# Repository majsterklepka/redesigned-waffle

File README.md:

# redesigned-waffle
mkII AVRISP programmer clone

Projekt klonu wykonany w KiCad. Pewne elementy schematu ideowego wymagają bibliotek, są one dostępne tu: [majsterklepka/expert-waffle](https://github.com/majsterklepka/expert-waffle "eeschema KiCad Libraries"), należy sklonować repo i zainstalować wymagane biblioteki ręcznie.

Klon wykorzystuje framework [LUFA](https://github.com/abcminiuser/lufa "LUFA")

Schemat ideowy => [diagram](/avrisp-mkII-clone/avrisp-mkII-clone.pdf "diagram")

> **2020.04.02**   Dodałem pliki Gerber z rysunkiem płytki drukowanej

## Jak wgrać firmware?

Oczywiście, najpier należy je zdbudować, potem do wgrania firmware wykorzystuje się narzędzie `dfu-util` dostępne chyba w każdej dystrybucji Linuksa i xxxBSD.

## Jak wgrać firmware?

```
dfu-util --upload firmware.hex

gdzie:
firmware.hex - plik HEX z firmware, LUFA/Projects/AVRISP-MKII/

```

Tyle w skrócie, czasem należy podać dodatkowe dane, takie jak `<vendor>:<product>`. Te dane podaje się z opcją `--device`, więcej informacji:

```
dfu-util --help
```

## Credits

Jako taki projekt jest znany w Sieci, istnieje wiele dostępnych modyfikacji, tu jest jedna z nich.

- [MIT](https://raw.githubusercontent.com/majsterklepka/redesigned-waffle/master/LICENSE "MIT License content")

Ten projekt to moja wersja, moja wizja tego popularnego programatora.

_MSc. Paweł Sobótka (SQ7EQE)_

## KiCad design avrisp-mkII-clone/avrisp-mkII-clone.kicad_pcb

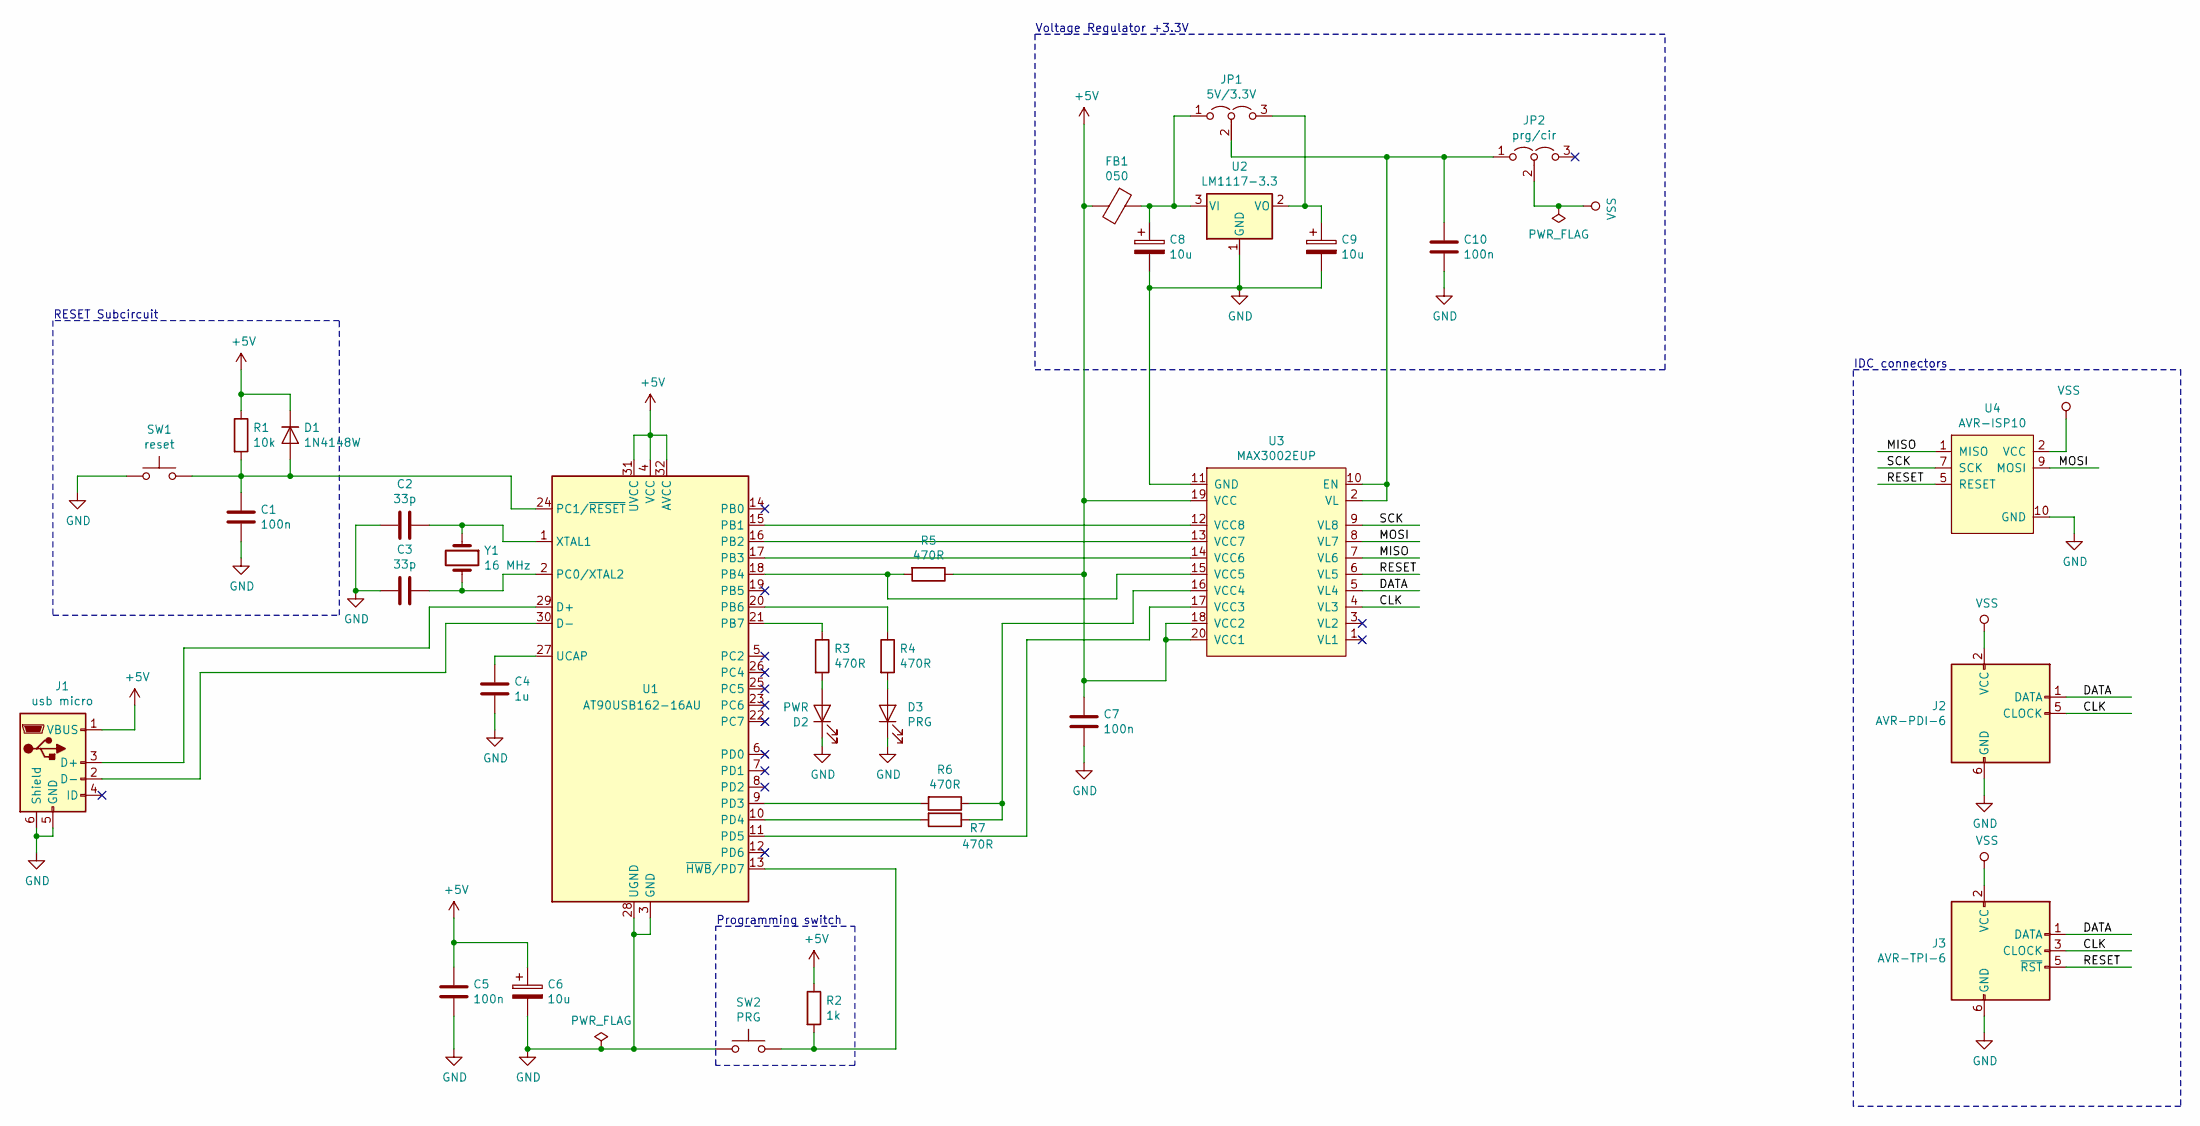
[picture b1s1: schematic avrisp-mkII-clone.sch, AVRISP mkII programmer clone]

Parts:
C1, C5, C7, C10: 100n; C_0805_2012Metric_Pad1.15x1.40mm_HandSolder
C2, C3: 33p; C_0805_2012Metric_Pad1.15x1.40mm_HandSolder
C4: 1u; C_0805_2012Metric_Pad1.15x1.40mm_HandSolder
C6, C8, C9: 10u; CP_EIA-7343-15_Kemet-W_Pad2.25x2.55mm_HandSolder
D1: 1N4148W; D_SOD-123
D2: PWR; LED_D3.0mm
D3: PRG; LED_D3.0mm
FB1: 050; R_1206_3216Metric_Pad1.42x1.75mm_HandSolder
J1: usb micro; USB_Micro-B_Molex_47346-0001
J2: AVR-PDI-6; IDC-Header_2x03_P2.54mm_Vertical
J3: AVR-TPI-6; IDC-Header_2x03_P2.54mm_Vertical
JP1: 5V/3.3V; PinHeader_1x03_P2.54mm_Vertical
JP2: prg/cir; PinHeader_1x03_P2.54mm_Vertical
R1: 10k; R_0805_2012Metric_Pad1.15x1.40mm_HandSolder
R2: 1k; R_0805_2012Metric_Pad1.15x1.40mm_HandSolder
R3, R4, R5, R6, R7: 470R; R_0805_2012Metric_Pad1.15x1.40mm_HandSolder
SW1: reset; SW_PUSH_6mm_H5mm
SW2: PRG; SW_PUSH_6mm_H5mm
U1: AT90USB162-16AU; TQFP-32_7x7mm_P0.8mm
U2: LM1117-3.3; SOT-223
U3: MAX3002EUP; TSSOP-20_4.4x6.5mm_P0.65mm
U4: AVR-ISP10; IDC-Header_2x05_P2.54mm_Vertical
Y1: 16 MHz; Crystal_SMD_HC49-SD_HandSoldering

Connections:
+5V: C5.1, C6.1, C7.2, D1.1 (K), FB1.2, J1.1 (VBUS), R1.1, R2.1, R5.1, U1.4 (VCC), U1.31 (UVCC), U1.32 (AVCC), U3.18 (VCC2), U3.19 (VCC), U3.20 (VCC1)
/CLK: J2.5 (CLOCK), J3.3 (CLOCK), U3.4 (VL3)
/DATA: J2.1 (DATA), J3.1 (DATA), U3.5 (VL4)
/MISO: U3.7 (VL6), U4.1 (MISO)
/MOSI: U3.8 (VL7), U4.9 (MOSI)
/RESET: J3.5 (~RST), U3.6 (VL5), U4.5 (RESET)
/SCK: U3.9 (VL8), U4.7 (SCK)
GND: C1.1, C2.2, C3.2, C4.2, C5.2, C6.2, C7.1, C8.2, C9.2, C10.1, D2.1 (K), D3.1 (K), J1.5 (GND), J1.6 (Shield), J2.6 (GND), J3.6 (GND), SW1.1, SW2.1, U1.3 (GND), U1.28 (UGND), U2.1 (GND), U3.11 (GND), U4.10 (GND)
unnamed: C1.2, D1.2 (A), R1.2, SW1.2, U1.24 (PC1/~RESET)
unnamed: C2.1, U1.1 (XTAL1), Y1.1
unnamed: C3.1, U1.2 (PC0/XTAL2), Y1.2
unnamed: C4.1, U1.27 (UCAP)
unnamed: C8.1, FB1.1, JP1.1 (A), U2.3 (VI)
unnamed: C9.1, JP1.3 (B), U2.2 (VO)
unnamed: C10.2, JP1.2 (C), JP2.1 (A), U3.2 (VL), U3.10 (EN)
unnamed: D2.2 (A), R3.2
unnamed: D3.2 (A), R4.2
unnamed: J1.2 (D-), U1.30 (D-)
unnamed: J1.3 (D+), U1.29 (D+)
unnamed: R2.2, SW2.2, U1.13 (~HWB~/PD7)
unnamed: R3.1, U1.21 (PB7)
unnamed: R4.1, U1.20 (PB6)
unnamed: R5.2, U1.18 (PB4), U3.15 (VCC5)
unnamed: R6.1, R7.1, U3.16 (VCC4)
unnamed: R6.2, U1.9 (PD3)
unnamed: R7.2, U1.10 (PD4)
unnamed: U1.11 (PD5), U3.17 (VCC3)
unnamed: U1.15 (PB1), U3.12 (VCC8)
unnamed: U1.16 (PB2), U3.13 (VCC7)
unnamed: U1.17 (PB3), U3.14 (VCC6)
VSS: J2.2 (VCC), J3.2 (VCC), JP2.2 (C), U4.2 (VCC)

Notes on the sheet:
RESET Subcircuit
Voltage Regulator +3.3V
IDC connectors
Programming switch

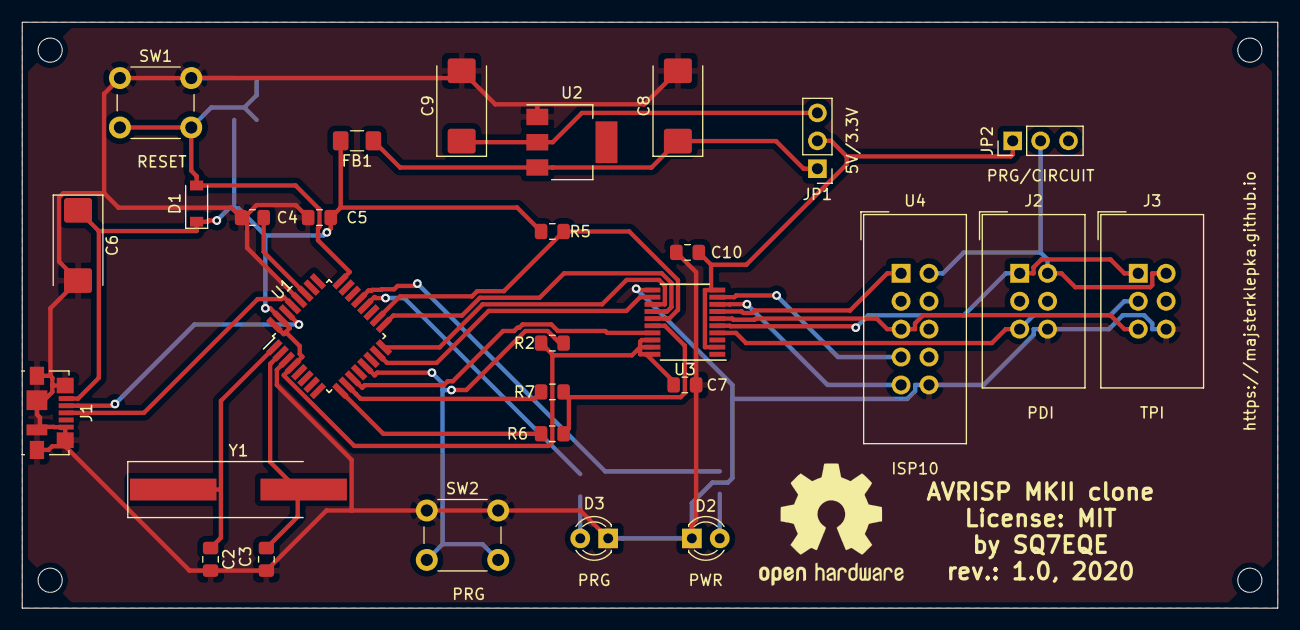
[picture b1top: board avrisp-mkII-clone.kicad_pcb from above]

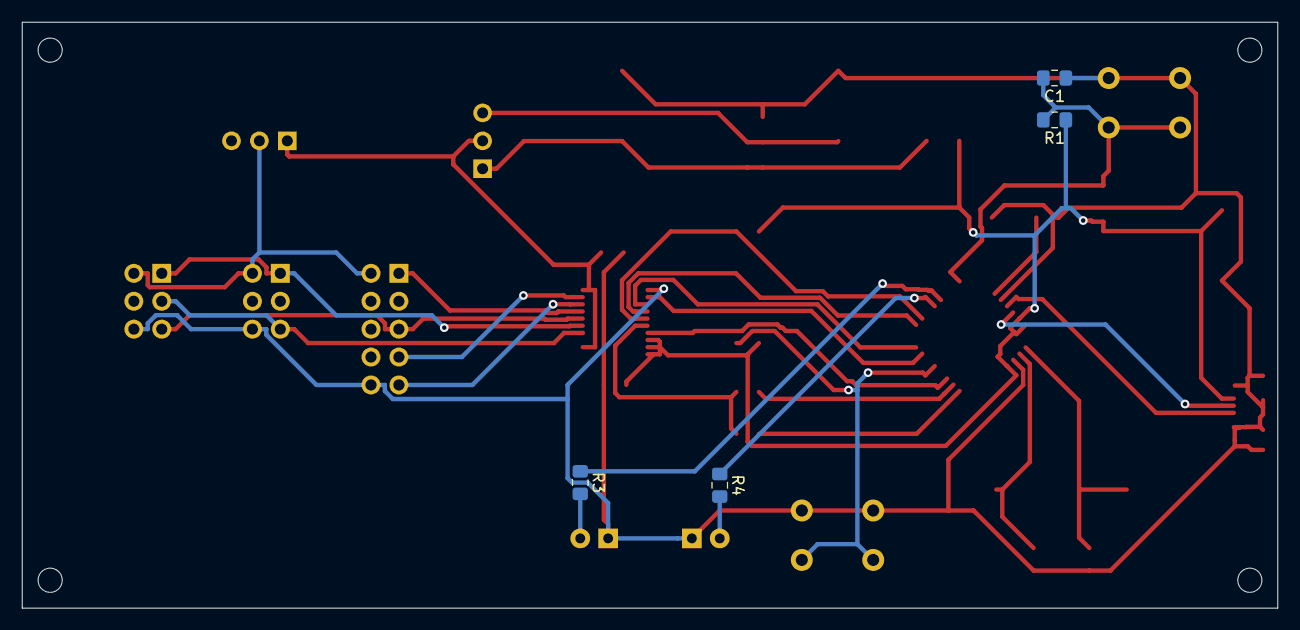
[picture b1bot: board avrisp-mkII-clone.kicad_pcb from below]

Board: 2 copper layers, 114.3 x 53.3 mm, 37 parts (4 on the bottom side), 31 nets.

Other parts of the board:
M1, M2, M3, M4: MountingHole_2.2mm_M2_DIN965

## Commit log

2020-03-23 Create LICENSE
2020-03-24 new file
2020-03-24 Add lufa submodule
2020-03-24 Add expert-waffle submodule
2020-04-02 add Gerber file
2020-04-02 add file
2020-04-02 update project file
2020-04-02 update file
2020-04-03 Set theme jekyll-theme-minimal
2020-04-03 add new file
2020-04-03 update file
2020-04-07 update file, change size & redesign
2020-08-17 included cookie policy script link
